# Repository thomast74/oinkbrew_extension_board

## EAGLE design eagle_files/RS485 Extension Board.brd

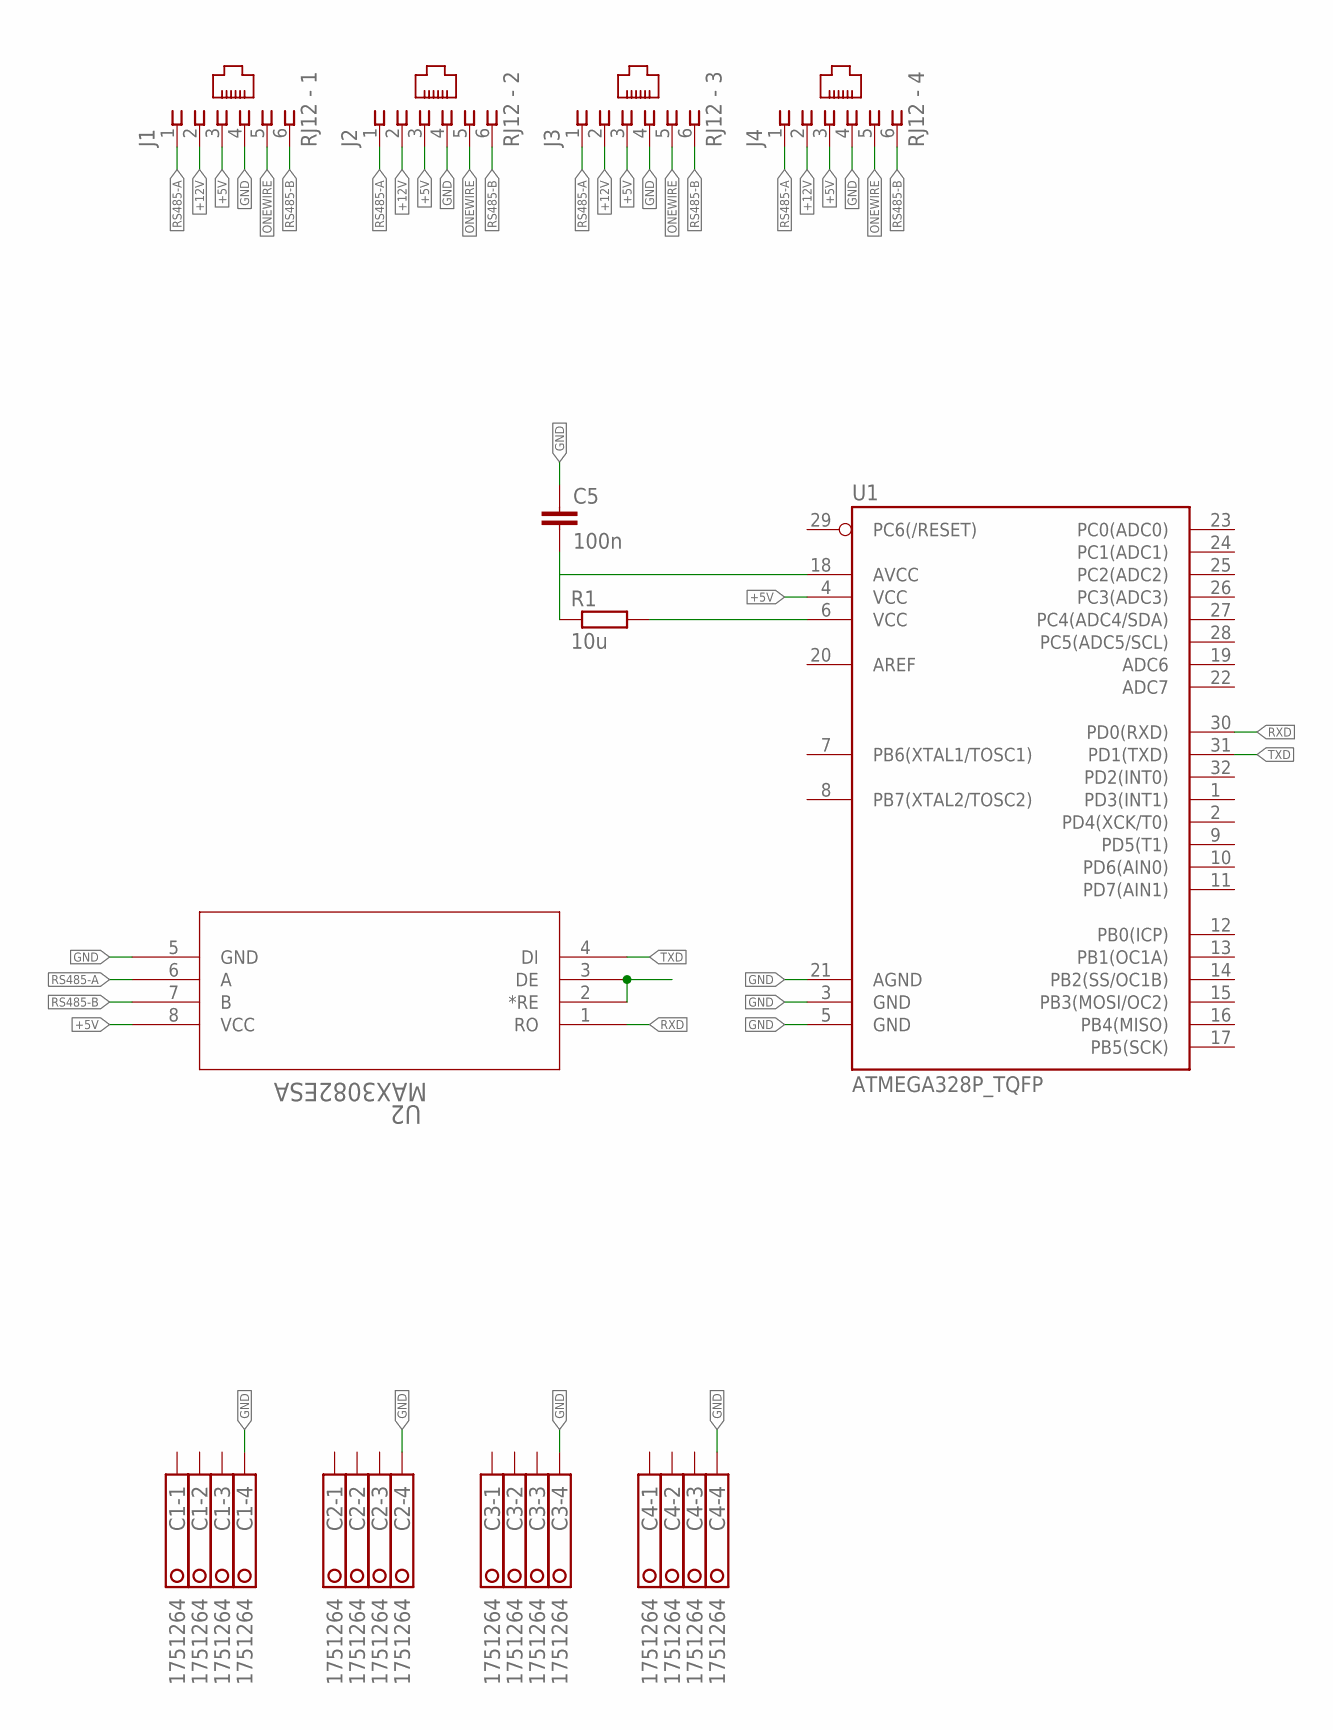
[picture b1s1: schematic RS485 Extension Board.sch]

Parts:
C1, C2, C3, C4: 1751264
C5: 100n; C0805
J1: RJ12 - 1; 520250-3
J2: RJ12 - 2; 520250-3
J3: RJ12 - 3; 520250-3
J4: RJ12 - 4; 520250-3
R1: 10u; M0805
U1: ATMEGA328P_TQFP; TQFP32-08
U2: MAX3082ESA; 21-0041B_8

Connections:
+5V: C5.2, J1.3, J2.3, J3.3, J4.3, R1.1, U1.4 (VCC), U1.18 (AVCC), U2.8 (VCC)
+12V: J1.2, J2.2, J3.2, J4.2
GND: C1.4, C2.4, C3.4, C4.4, C5.1, J1.4, J2.4, J3.4, J4.4, U1.3 (GND), U1.5 (GND), U1.21 (AGND), U2.5 (GND)
unnamed: U2.2 (*RE), U2.3 (DE)
unnamed: R1.2, U1.6 (VCC)
ONEWIRE: J1.5, J2.5, J3.5, J4.5
RS485-A: J1.1, J2.1, J3.1, J4.1, U2.6 (A)
RS485-B: J1.6, J2.6, J3.6, J4.6, U2.7 (B)
RXD: U1.30 (PD0(RXD)), U2.1 (RO)
TXD: U1.31 (PD1(TXD)), U2.4 (DI)

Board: 2 copper layers, 12 parts (0 on the bottom side), 10 nets, no tracks yet.

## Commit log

2016-02-17 Ignore not required files
2016-02-17 Initial schema and board files
2016-02-17 add connector and ic

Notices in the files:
parts and their libraries:
SparkFun-DigitalIC: Licensing: Creative Commons ShareAlike 4.0 International - https://creativecommons.org/licenses/by-sa/4.0
